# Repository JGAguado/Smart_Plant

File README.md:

# Smart Plant

**See how your plant is doing — on its own e-paper label and in Home Assistant.**

Smart Plant measures soil moisture, light, temperature and humidity. Place it
in your plant pot, read the measurements on the 2.9-inch e-paper display,
and connect it to Home Assistant with ESPHome.

**[Get started](https://smart-plant.readthedocs.io/en/v2r1/getting_started.html)**
· **[Create your plant label](https://github.com/JGAguado/Label-maker)**
· **[Get a board](https://www.elecrow.com/smart-plant.html)**
· **[Read the documentation](https://smart-plant.readthedocs.io/en/v2r1/)**

## A useful label for every plant

- **Check the soil and surroundings.** Read soil moisture, ambient light,
  air temperature and relative humidity.
- **Read it at the pot.** The e-paper screen shows the last displayed readings
  while the device sleeps.
- **Make it yours.** Give each plant its own name, illustration and gauge
  background with the companion Label-maker project.
- **Connect to Home Assistant.** Choose the native ESPHome API or retained
  MQTT readings for devices that spend most of their time asleep.
- **Run on battery.** The firmware sleeps between measurement cycles.
  The hardware also supports an optional solar cell.

## Start with one plant

1. [Get a board](https://www.elecrow.com/smart-plant.html), or use the
   [hardware design files](Design/) to explore the board.
2. Follow the [getting-started guide](https://smart-plant.readthedocs.io/en/v2r1/getting_started.html)
   and [ESPHome programming guide](https://smart-plant.readthedocs.io/en/v2r1/programming.html).
3. Set your Wi-Fi credentials and calibrate the soil sensor for your setup.
4. Add your own label background, then install the firmware.

The [standalone configuration](docs/source/files/configuration.yaml) is the
starting point for a single device. Read the
[safety instructions](https://smart-plant.readthedocs.io/en/v2r1/safety.html)
before assembly and flashing.

## Create your plant label

The companion **[Label-maker](https://github.com/JGAguado/Label-maker)**
generates printable plant labels and e-paper backgrounds from JSON or YAML
templates. Use it to add a plant name and illustration to your display.

Follow the [step-by-step label guide](docs/source/labels.rst).
Start with the [plant examples and generator](https://github.com/JGAguado/Label-maker/tree/main/1_Plants),
then follow the programming guide to use the resulting background image.
The firmware draws the live readings over that image.

## Connect one plant or several

| Setup | Starting point | During deep sleep |
| --- | --- | --- |
| One device with the native ESPHome API | [Standalone configuration](docs/source/files/configuration.yaml) | No network response; entity availability depends on Home Assistant setup. |
| Several devices with retained MQTT readings | [MQTT example](examples/multi-device/my-lemon-tree.yaml) | Last published readings remain available. |
| Shared packages with the native ESPHome API | [API example](examples/multi-device/my-lemon-tree-api.yaml) | No network response; entity availability depends on Home Assistant setup. |

The [multi-device guide](examples/multi-device/README.md) explains the shared
hardware core and transport profiles. Each device sets its identity and
credentials. Calibration and label images use shared defaults unless overridden.

## Explore the hardware

Smart Plant combines an ESP32-S2, a soil-moisture probe, environmental sensors
and an e-paper display. The repository includes board design files and
printable enclosure models.

- [Board design](Design/)
- [Enclosure models](Enclosure/)
- [Schematics and supporting files](Documentation/)
- [Technical specifications](https://smart-plant.readthedocs.io/en/v2r1/specs.html)
- [Assembly guide](https://smart-plant.readthedocs.io/en/v2r1/assembly.html)

## Questions and contributions

Use [Discussions](https://github.com/JGAguado/Smart_Plant/discussions) for
questions and ideas. Report reproducible problems in
[Issues](https://github.com/JGAguado/Smart_Plant/issues).

Contributions to firmware, documentation and examples are welcome. Describe
the problem, the change and how you verified it in your pull request.

Created by [J. G. Aguado](https://github.com/JGAguado), with contributions
from the community.

## License

This project uses [CC BY-NC-SA 4.0](LICENSE). See the license for attribution,
non-commercial use and sharing requirements.

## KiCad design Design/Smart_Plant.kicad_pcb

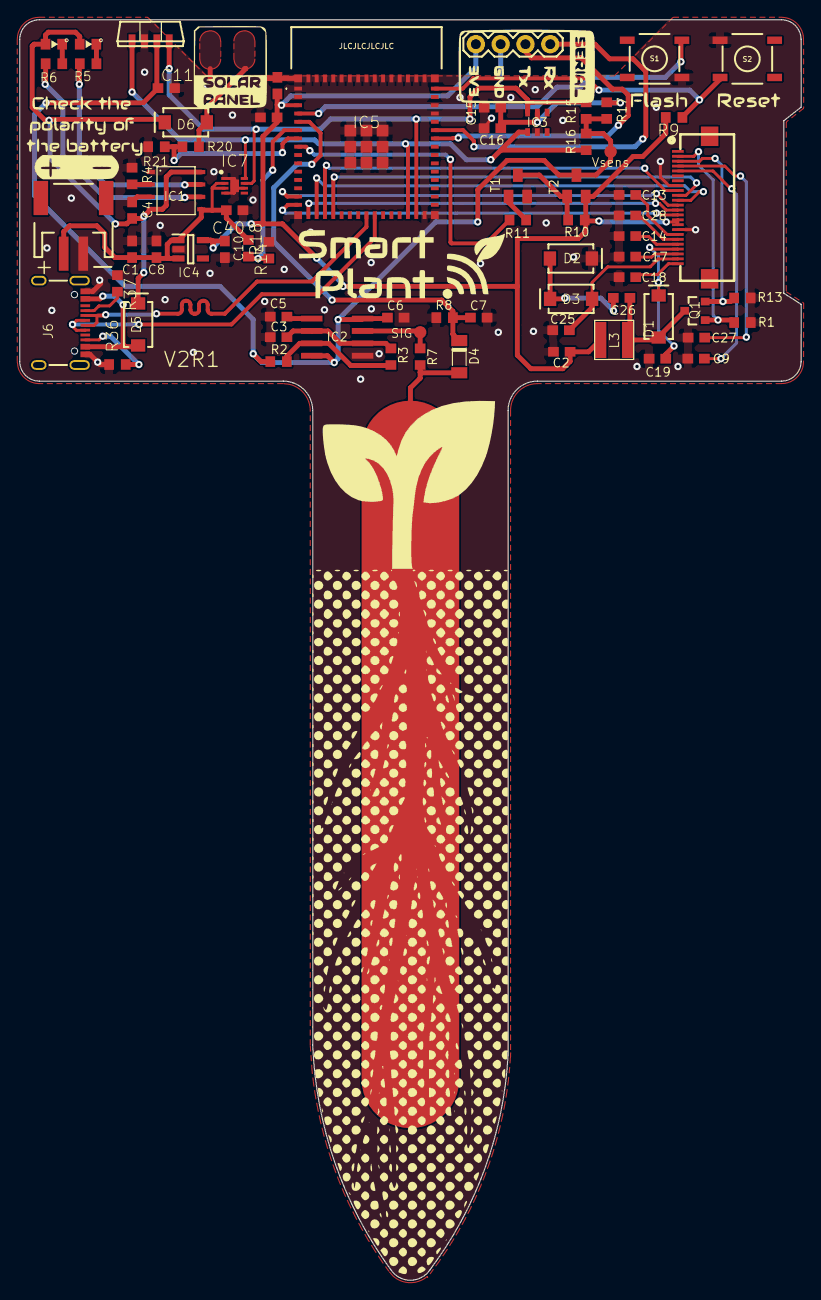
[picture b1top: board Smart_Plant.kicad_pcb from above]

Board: 2 copper layers, 80.0 x 129.1 mm, 73 parts (0 on the bottom side), 53 nets.

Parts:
C1, C4, C8, C10, C16, C20: 10uF; C0603
C2, C26: 4.7uF; C0603
C3: 0.47nF; C0603
C5: 10nF; C0603
C6, C11: 100nF; C0603
C7, C9, C13, C14, C17, C18, C19, C25, C27, C28: 1uF; C0603
C12, C15, C40: 0.1uF; C0603
D1, D2, D3, D5, D6: SS14; SMA-DIODE
D4: LL4148; LL-34
FPC0: E-PAPER-FPC; FPC_24_0.5MM
IC1: TP4056; SOT23-8
IC2: TLC555CDR; SO08
IC3: AHT20
IC4: RT9080-33GJ5; SOT94P280X100-5N
IC5: ESP32-S2-MINI-1-N4R2; ESP32S2MINI1N4R2
IC6: VEML7700-TR
IC7: MAX17048G+T10; SON50P200X200X80-9N
J1: JST-2-SMD
J5: 1X04
J6: USB-C; USB-C-16P-4LAYER-ISOLATED
L3: 10uH; INDUCTOR_4X4MM_NR401
LED1: Red; LED_0603
LED2: Green; LED_0603
Q1: IRLML0100; SOT23-3
R1, R7, R10, R15, R16: 10k; R0603
R2: 330R; R0603
R3: 1.5k; R0603
R4: 1.2k; R0603
R5: 1K; R0603
R6, R11: 1k; R0603
R8, R14, R18, R20: 1M; R0603
R9: 10K; R0603
R13: 0.47; R0603
R17: 220; R0603
R21: 240k; R0603
R36, R37: 5.1k; R0603
S1: Flash; TACTILE_SWITCH_SMD_5.2MM
S2: Reset; TACTILE_SWITCH_SMD_5.2MM
T1: MMBT2222A; SOT23
T2: LBSS84LT1G; SOT23
TP1, TP2: TPB1,27; B1,27

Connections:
3.3V: C2.1, C10.1, C12.1, C20.1, FPC0.15, FPC0.16, IC4.5, IC5.3, J5.1, L3.P$2, R9.2, R10.1, T2.2
+SOL: D6.A, R20.1
BATTERY: IC5.6, R14.2, R18.1
BUSY: FPC0.9, IC5.18
D+: IC5.24, J6.A6, J6.B6
D-: IC5.23, J6.A7, J6.B7
DC: FPC0.11, IC5.17
DISPCS: FPC0.12, IC5.14
GDR: FPC0.2, Q1.1, R1.1
GND: C1.2, C2.2, C3.2, C4.2, C5.1, C6.2, C7.2, C8.2, C9.1, C10.2, C11.2, C12.2, C13.1, C14.1, C15.2, C16.2, C17.1, C18.1, C19.2, C20.2, C25.2, C27.1, C28.1, C40.2, D2.C, FPC0.8, FPC0.17, IC1.1, IC1.3, IC2.1, IC3.5, IC4.2, IC5.1, IC5.2, IC5.30, IC5.42, IC5.43, IC5.46, IC5.47, IC5.48, IC5.49, IC5.50, IC5.51, IC5.52, IC5.53, IC5.54, IC5.55, IC5.56, IC5.57, IC5.58, IC5.59, IC5.60, IC5.61, IC5.62, IC5.63, IC5.64, IC5.65, IC5.66, IC5.67, IC5.68, IC5.69, IC5.70, IC5.71, IC5.72, IC5.73, IC6.3, IC7.1, IC7.4, IC7.6, IC7.9, J1.2, J5.2, J6.GND, J6.GND2, R1.2, R4.1, R8.2, R13.2, R18.2, R21.1, R36.1, R37.1, S1.1, S2.1, T1.2
IO0: IC5.4, S1.3
MOISTURE: C7.1, D4.C, IC5.5, R8.1
MOSI: FPC0.14, IC5.15
unnamed: IC1.6, R6.2
unnamed: LED1.C, R5.1
unnamed: LED2.C, R6.1
unnamed: IC1.2, R4.2
unnamed: C3.1, IC2.2, IC2.6, R3.2
unnamed: IC1.7, R5.2
unnamed: IC2.7, R2.2, R3.1
unnamed: C5.2, IC2.5
unnamed: R10.2, T1.3, T2.1
unnamed: C15.1, C16.1, IC3.2, R17.2
unnamed: C9.2, FPC0.5
unnamed: C13.2, FPC0.18
unnamed: C14.2, FPC0.20
unnamed: C17.2, FPC0.22
unnamed: C18.2, FPC0.24
unnamed: C26.2, D2.A, D3.C
unnamed: C26.1, D1.A, L3.P$1, Q1.3
unnamed: R11.2, T1.1
unnamed: C27.2, FPC0.4
unnamed: C28.2, FPC0.19
unnamed: J6.B5, R36.2
unnamed: J6.A5, R37.2
OUT: IC2.3, R7.2, TP1.TP
PROBE: D4.A, R7.1
RESE: FPC0.3, Q1.2, R13.1
RESET: FPC0.10, IC5.19
RST: IC5.45, R9.1, S2.3
RX: IC5.40, J5.4
SCL: IC3.3, IC5.29, IC6.1, IC7.7, R15.2
SCLK: FPC0.13, IC5.16
SDA: IC3.4, IC5.28, IC6.4, IC7.8, R16.2
SENS: IC5.8, R11.1
TX: IC5.39, J5.3
VBAT: C1.1, C8.1, C40.1, IC1.5, IC4.1, IC4.3, IC7.2, IC7.3, J1.1, R14.1
VGH: C19.1, D1.C, FPC0.21
VGL: C25.1, D3.A, FPC0.23
VIN: C4.1, D5.C, D6.C, IC1.4, IC1.8, LED1.A, LED2.A
VSENS: C6.1, C11.1, IC2.4, IC2.8, IC6.2, R2.1, R15.1, R16.1, R17.1, T2.3, TP2.TP
VSOLAR: IC5.7, R20.2, R21.2
V_USB: D5.A, J6.VBUS1, J6.VBUS2

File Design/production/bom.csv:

Designator,Footprint,Quantity,Value,LCSC Part #
"C1, C10, C16, C20, C4, C8",C0603,6,10uF,
"C11, C6",C0603,2,100nF,
"C12, C15, C40",C0603,3,0.1uF,
"C13, C14, C17, C18, C19, C25, C27, C28, C7, C9",C0603,10,1uF,
"C2, C26",C0603,2,4.7uF,
C3,C0603,1,0.47nF,
C5,C0603,1,10nF,
"D1, D2, D3, D5, D6",SMA-DIODE,5,SS14,
D4,LL-34,1,LL4148,
FPC,FPC_24_0.5MM,1,E-PAPER-FPC,
IC1,SOT23-8,1,TP4056,
IC2,SO08,1,TLC555CDR,
IC3,AHT20,1,AHT20,
IC4,SOT94P280X100-5N,1,RT9080-33GJ5,
IC5,ESP32S2MINI1N4R2,1,ESP32-S2-MINI-1-N4R2,
IC6,VEML7700-TR,1,VEML7700-TR,
IC7,SON50P200X200X80-9N,1,MAX17048G+T10,
J1,JST-2-SMD,1,,
J5,1X04,1,,
J6,USB-C-16P-4LAYER-ISOLATED,1,USB-C,
L3,INDUCTOR_4X4MM_NR401,1,10uH,
LED1,LED_0603,1,Red,
LED2,LED_0603,1,Green,
Q1,SOT23-3,1,IRLML0100,
"R1, R10, R15, R16, R7, R9",R0603,6,10k,
"R11, R5, R6",R0603,3,1k,
R13,R0603,1,0.47,
"R14, R18, R20, R8",R0603,4,1M,
R17,R0603,1,220,
R2,R0603,1,330R,
R21,R0603,1,240k,
R3,R0603,1,1.5k,
"R36, R37",R0603,2,5.1k,
R4,R0603,1,1.2k,
S1,TACTILE_SWITCH_SMD_5.2MM,1,Flash,
S2,TACTILE_SWITCH_SMD_5.2MM,1,Reset,
T1,SOT23,1,MMBT2222A,
T2,SOT23,1,LBSS84LT1G,
"TP1, TP2","B1,27",2,"TPB1,27",

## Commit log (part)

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2022-04-13 Added design files
2022-04-13 Added documentation
2022-04-13 Added design files for 'Kit' branch
2022-04-13 Added design files to 'Custom' branch

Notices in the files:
README.md:
License: CC BY-NC-SA 4.0
